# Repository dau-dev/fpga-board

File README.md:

# fpga-board
Based on the Xilinx AC701 and KC705 reference designs, this board was created to address the dearth of PCIe and DDR SODIMM capable board for less than $1000.

##Features
- Artix 7 FPGA (160k)
- 4GB DDR3 SODIMM
- 256MB Quad SPI Flash
- 8Kb IIC EEPROM
- SD Card Slot
- 2x 10/100/1000 Mbps Ethernet
- PCI Express 4 Lane
- Onboard JTAG
- Fixed Oscillator with differential 200MHz output
- User Programmable (IIC) Differential Oscillator (Range: 10MHz - 810 MHz, 156.250 MHz default)
- ATX Power 
- Half-Length PCI Card form factor

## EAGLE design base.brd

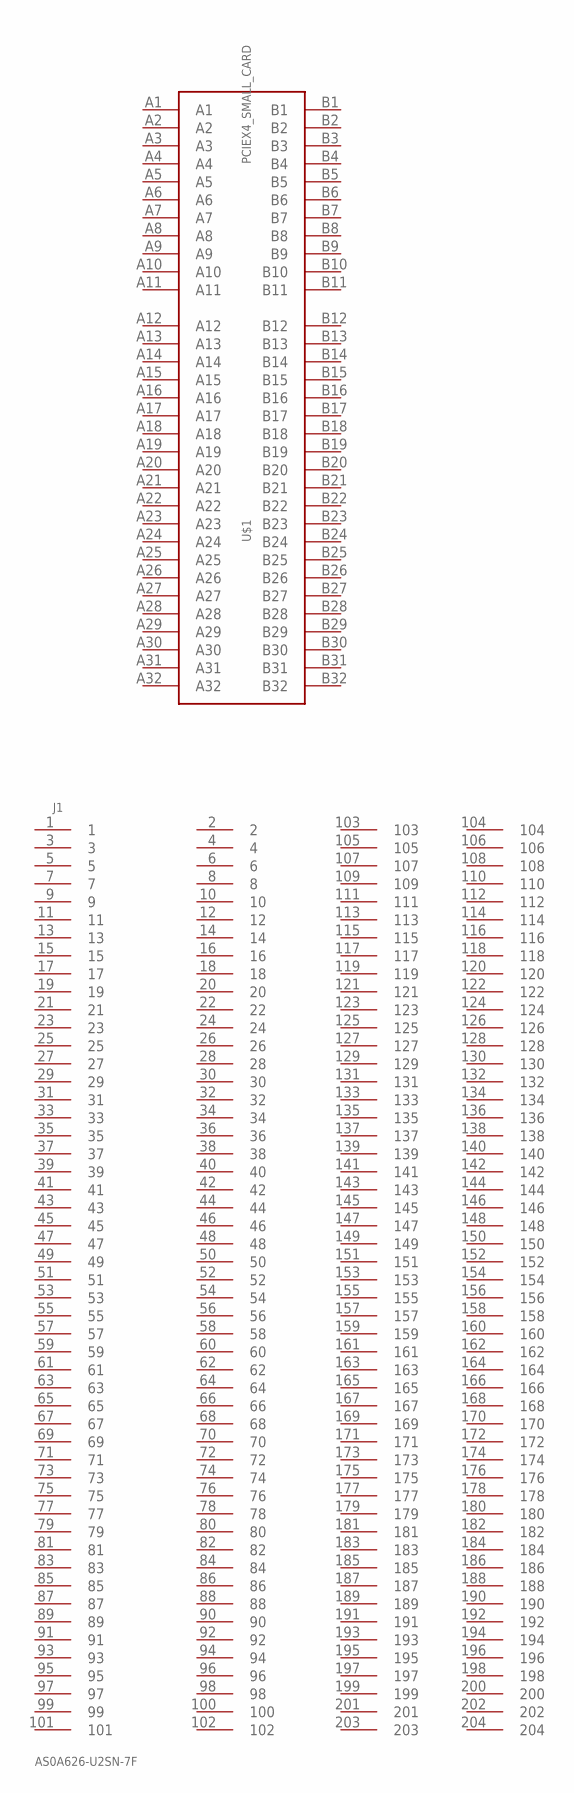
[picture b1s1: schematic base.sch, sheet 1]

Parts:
J1: AS0A626-U2SN-7F; FOXCONN_AS0A626-U2SN-7F
U$1: PCIEX4_SMALL_CARD

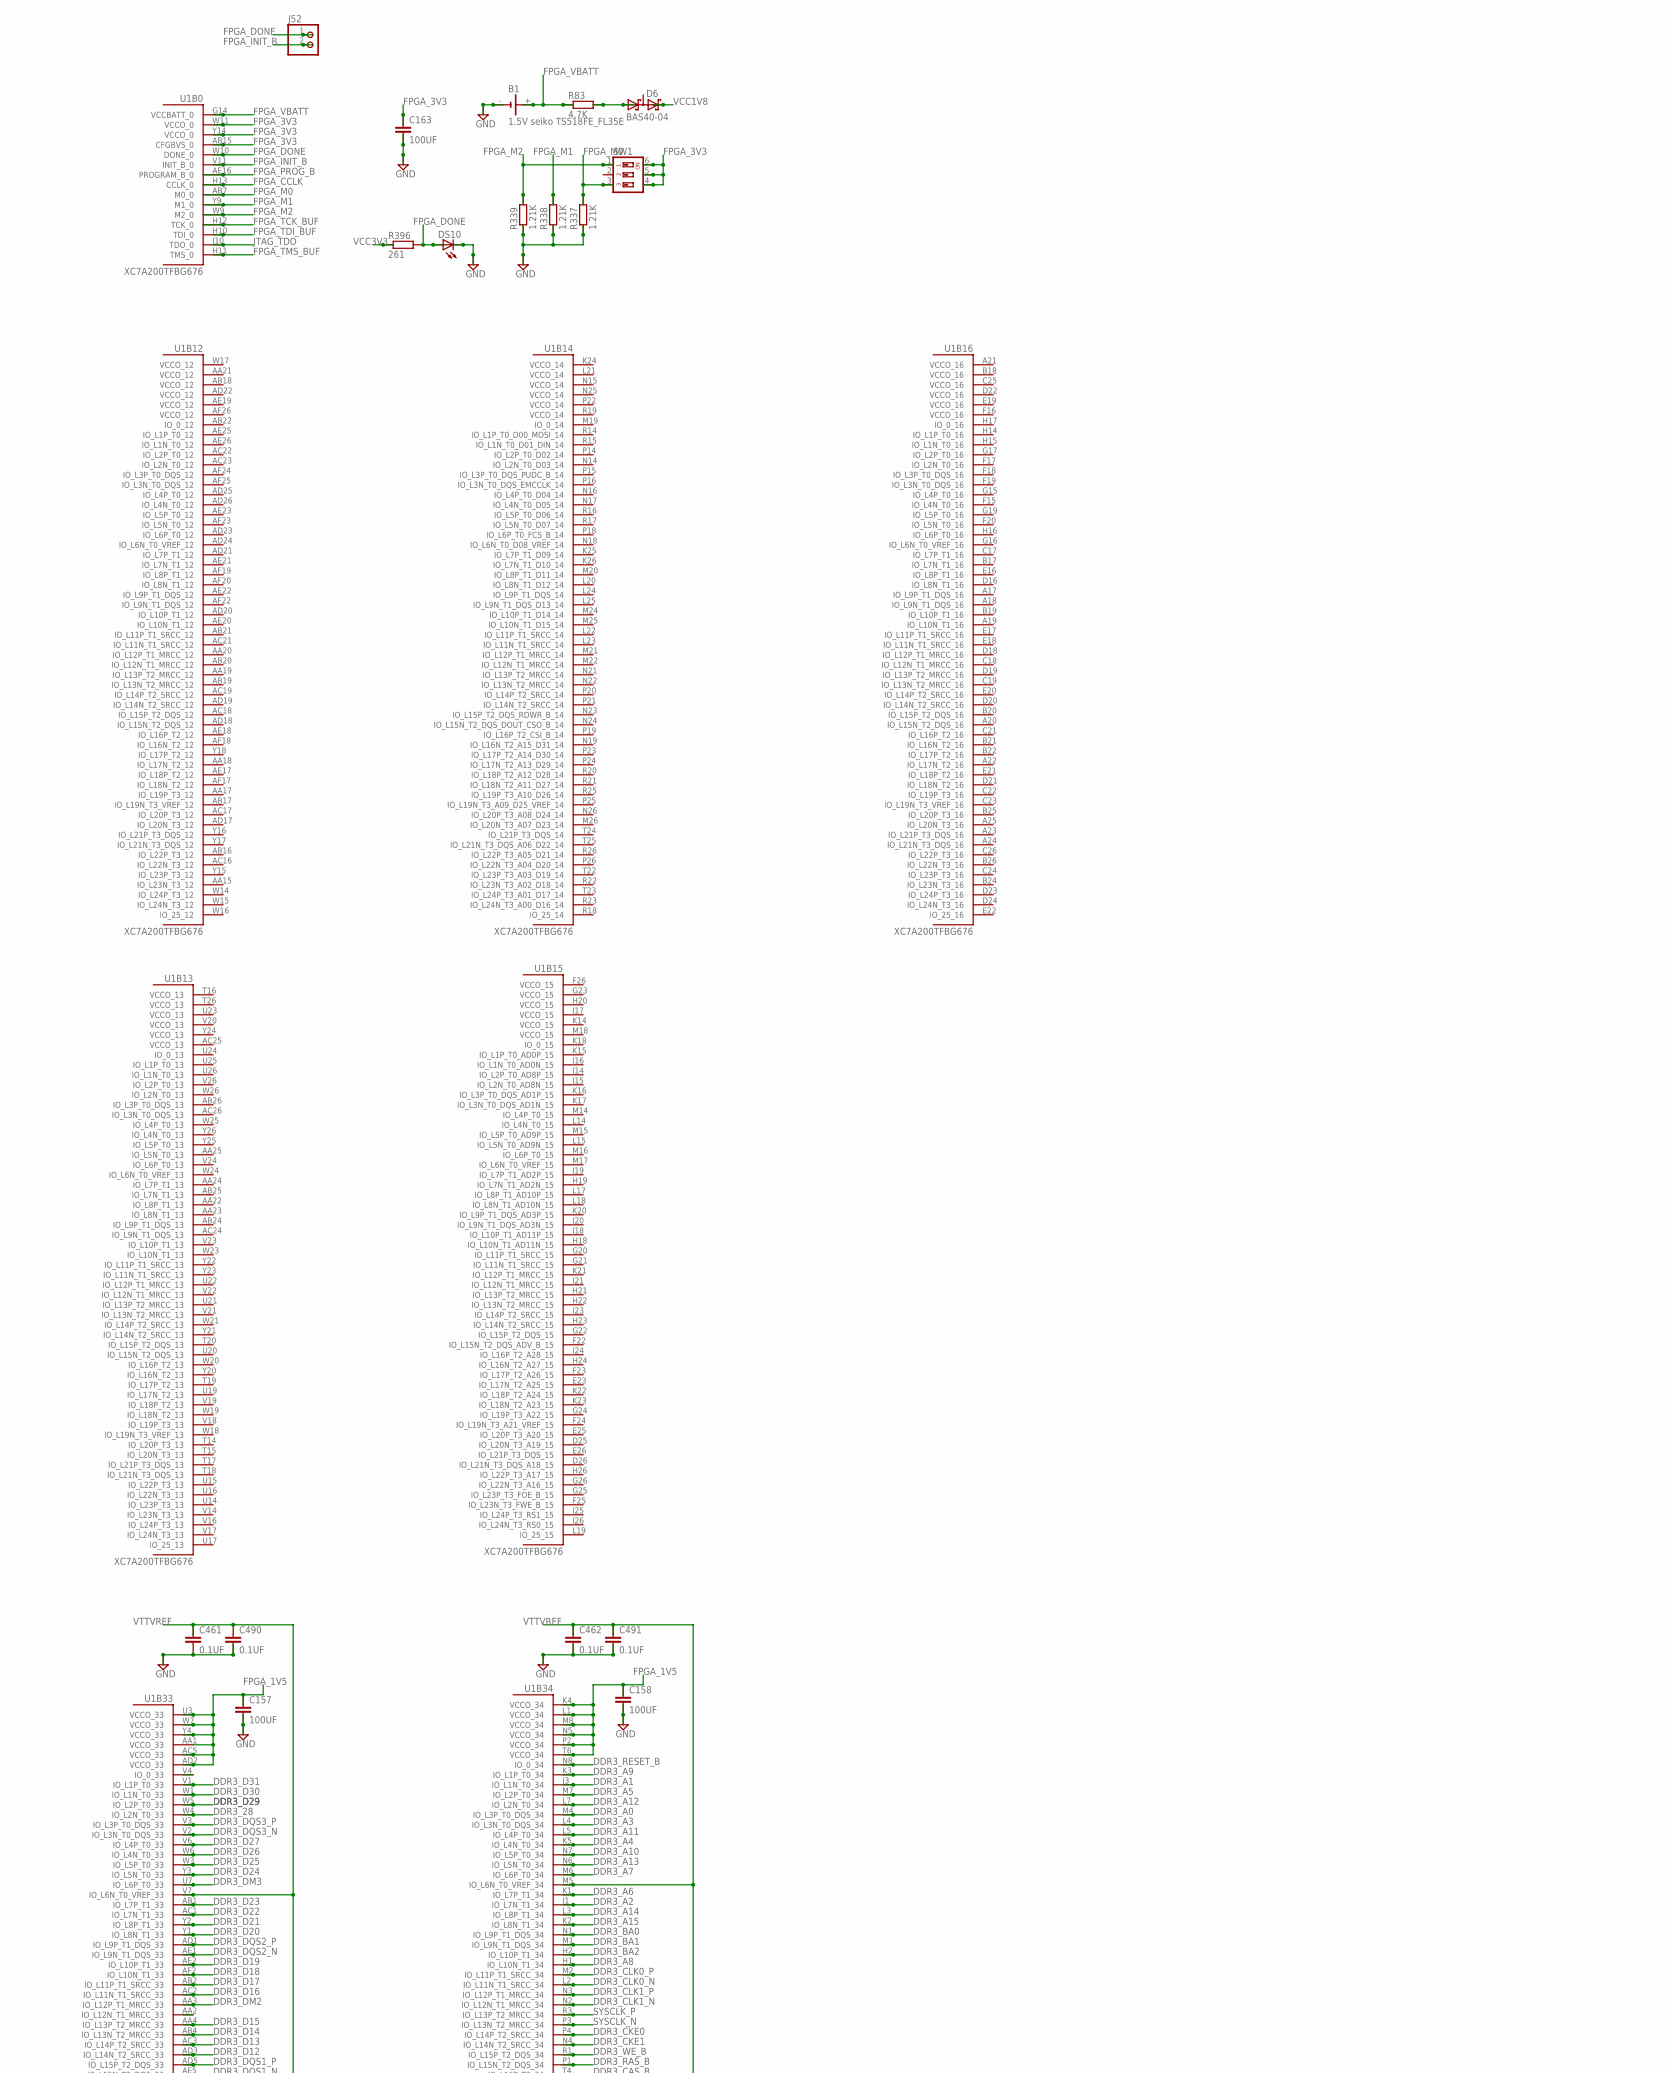
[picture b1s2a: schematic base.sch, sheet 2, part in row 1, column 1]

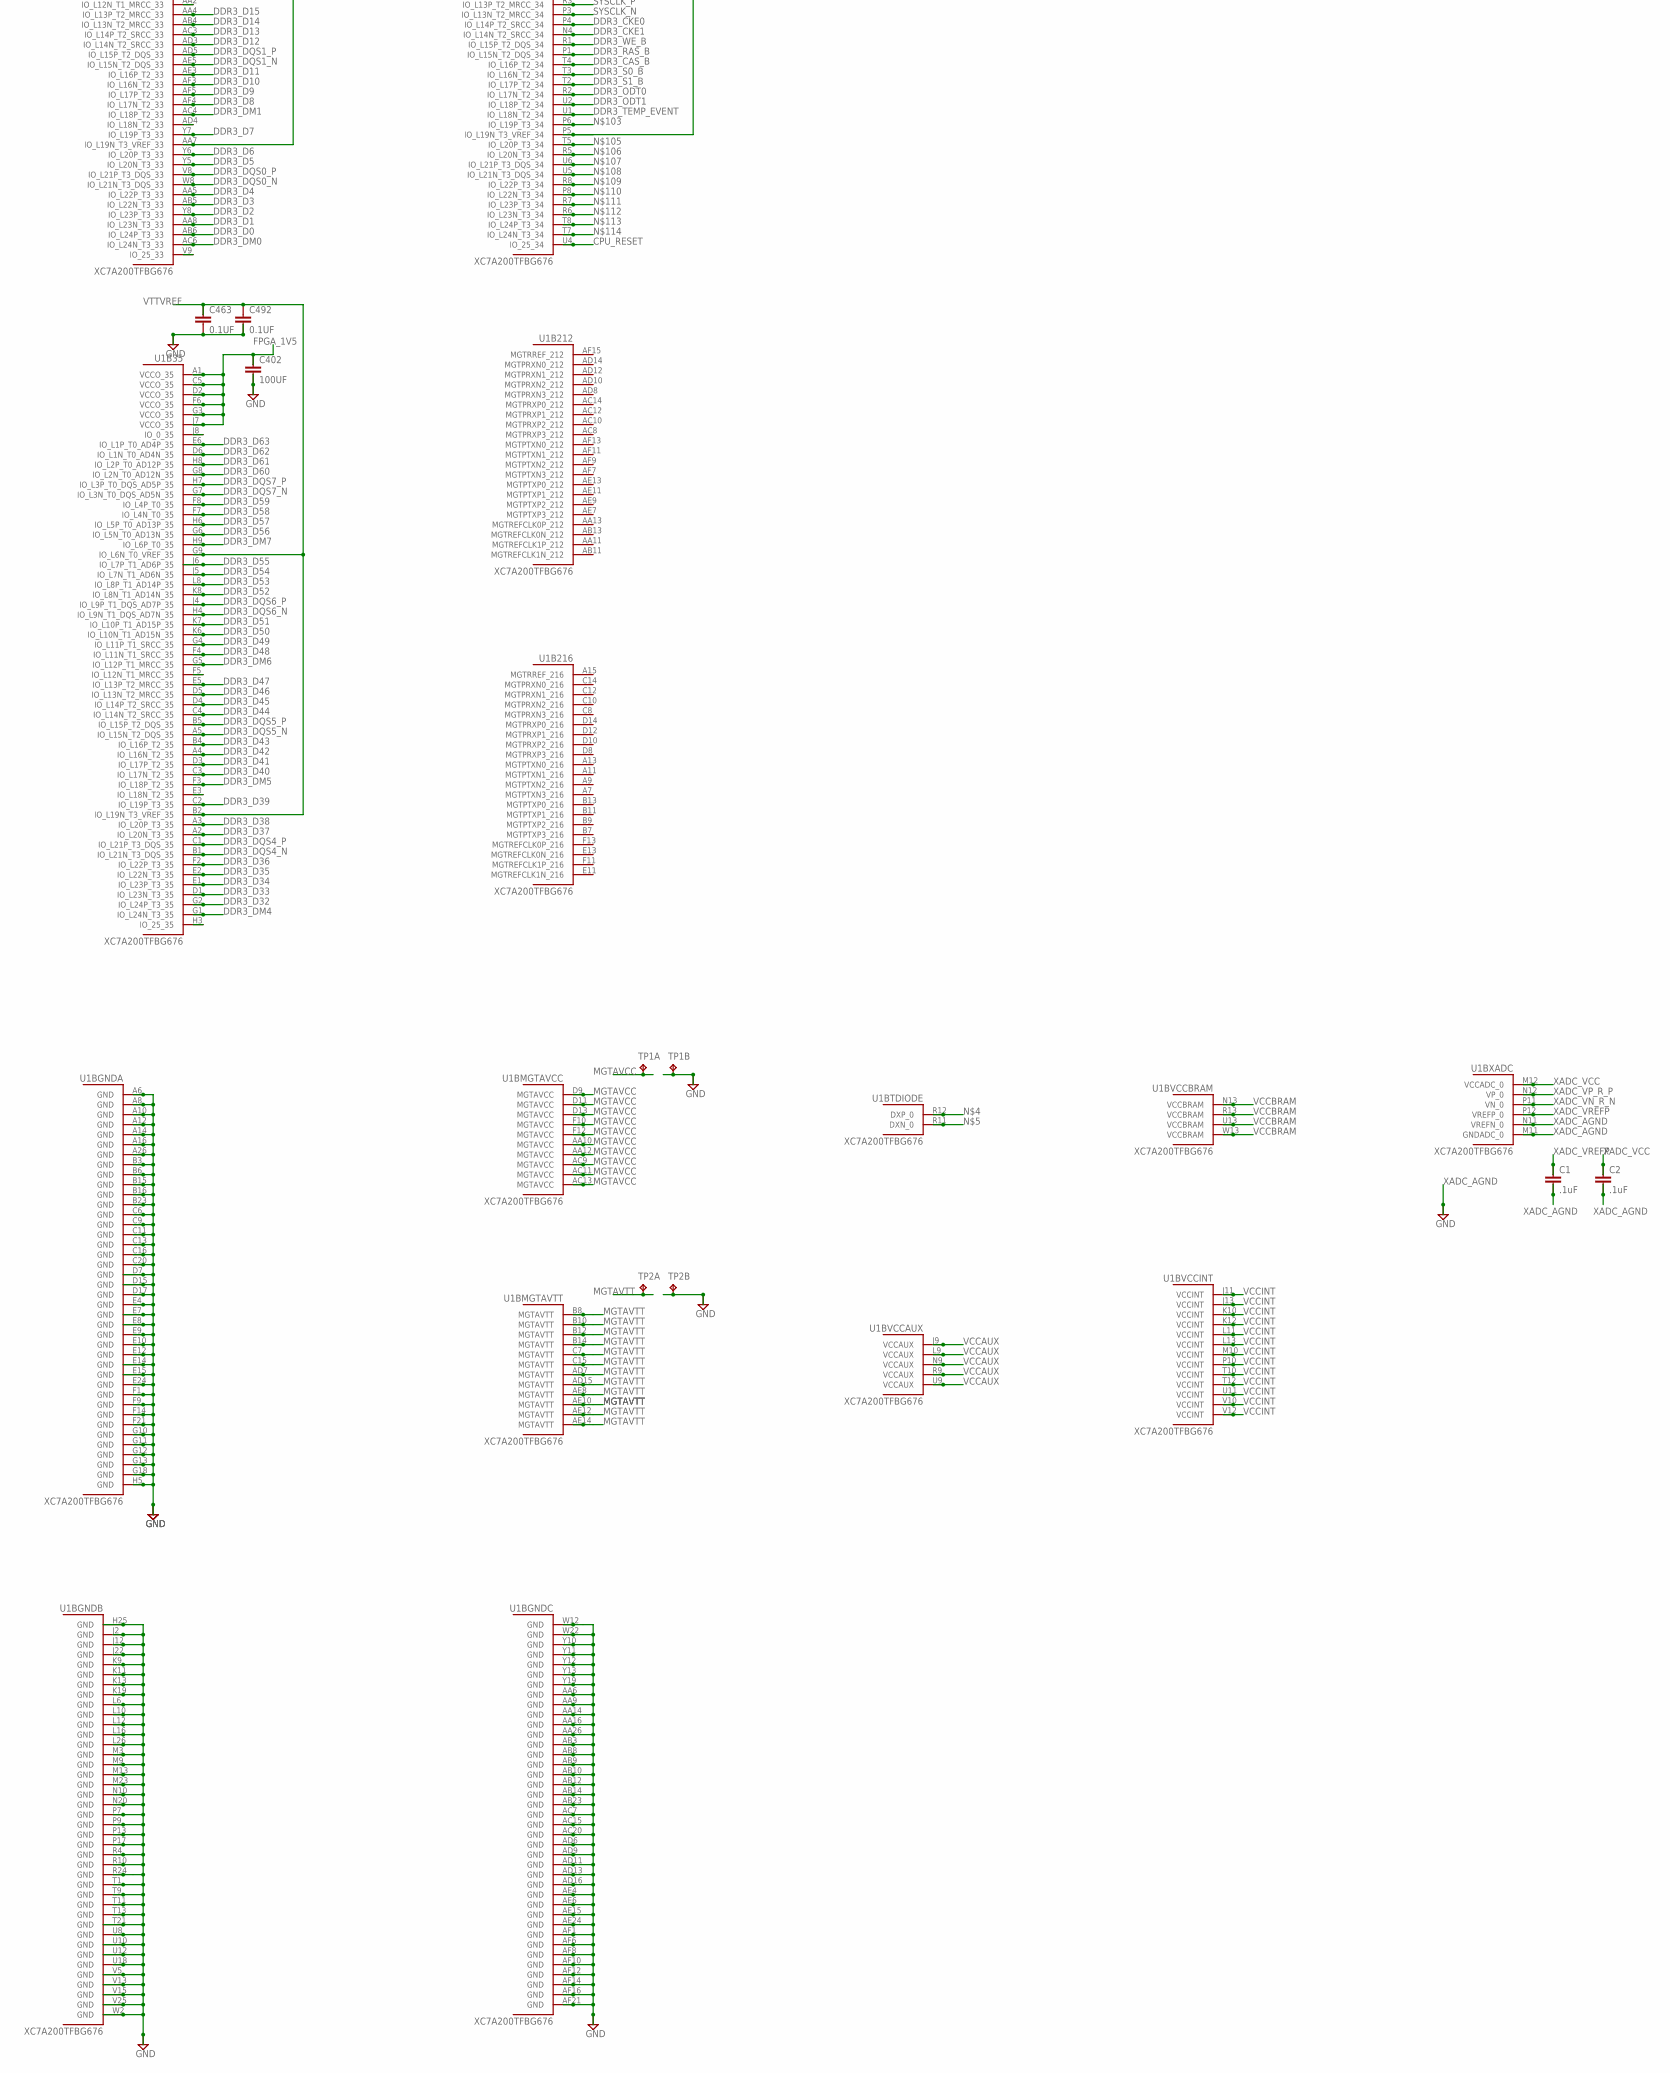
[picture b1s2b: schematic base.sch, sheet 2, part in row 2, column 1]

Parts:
B1: 1.5V seiko TS518FE_FL35E; CH291-1220LF
C1, C2: .1uF; C0402
C157, C158, C163, C402: 100UF; C1206
C461, C462, C463, C490, C491, C492: 0.1UF; C0402
D6: BAS40-04; SOT23
DS10: LEDCHIP-LED0603; CHIP-LED0603
J52: PINHD-1X2; 1X02
R83: 4.7K; R0402
R337, R338, R339: 1.21K; R0402
R396: 261; R0402
SW1: SWS003; SMS-003
TP1, TP2: TP2P2-38-17; P2-38-17
U1: XC7A200TFBG676; FF676

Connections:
CPU_RESET: U1.U4 (IO_25_34)
DDR3_28: U1.W4 (IO_L2N_T0_33)
DDR3_A0: U1.M4 (IO_L3P_T0_DQS_34)
DDR3_A1: U1.J3 (IO_L1N_T0_34)
DDR3_A2: U1.J1 (IO_L7N_T1_34)
DDR3_A3: U1.L4 (IO_L3N_T0_DQS_34)
DDR3_A4: U1.K5 (IO_L4N_T0_34)
DDR3_A5: U1.M7 (IO_L2P_T0_34)
DDR3_A6: U1.K1 (IO_L7P_T1_34)
DDR3_A7: U1.M6 (IO_L6P_T0_34)
DDR3_A8: U1.H1 (IO_L10N_T1_34)
DDR3_A9: U1.K3 (IO_L1P_T0_34)
DDR3_A10: U1.N7 (IO_L5P_T0_34)
DDR3_A11: U1.L5 (IO_L4P_T0_34)
DDR3_A12: U1.L7 (IO_L2N_T0_34)
DDR3_A13: U1.N6 (IO_L5N_T0_34)
DDR3_A14: U1.L3 (IO_L8P_T1_34)
DDR3_A15: U1.K2 (IO_L8N_T1_34)
DDR3_BA0: U1.N1 (IO_L9P_T1_DQS_34)
DDR3_BA1: U1.M1 (IO_L9N_T1_DQS_34)
DDR3_BA2: U1.H2 (IO_L10P_T1_34)
DDR3_CAS_B: U1.T4 (IO_L16P_T2_34)
DDR3_CKE0: U1.P4 (IO_L14P_T2_SRCC_34)
DDR3_CKE1: U1.N4 (IO_L14N_T2_SRCC_34)
DDR3_CLK0_N: U1.L2 (IO_L11N_T1_SRCC_34)
DDR3_CLK0_P: U1.M2 (IO_L11P_T1_SRCC_34)
DDR3_CLK1_N: U1.N2 (IO_L12N_T1_MRCC_34)
DDR3_CLK1_P: U1.N3 (IO_L12P_T1_MRCC_34)
DDR3_D0: U1.AB6 (IO_L24P_T3_33)
DDR3_D1: U1.AA8 (IO_L23N_T3_33)
DDR3_D2: U1.Y8 (IO_L23P_T3_33)
DDR3_D3: U1.AB5 (IO_L22N_T3_33)
DDR3_D4: U1.AA5 (IO_L22P_T3_33)
DDR3_D5: U1.Y5 (IO_L20N_T3_33)
DDR3_D6: U1.Y6 (IO_L20P_T3_33)
DDR3_D7: U1.Y7 (IO_L19P_T3_33)
DDR3_D8: U1.AF4 (IO_L17N_T2_33)
DDR3_D9: U1.AF5 (IO_L17P_T2_33)
DDR3_D10: U1.AF3 (IO_L16N_T2_33)
DDR3_D11: U1.AE3 (IO_L16P_T2_33)
DDR3_D12: U1.AD3 (IO_L14N_T2_SRCC_33)
DDR3_D13: U1.AC3 (IO_L14P_T2_SRCC_33)
DDR3_D14: U1.AB4 (IO_L13N_T2_MRCC_33)
DDR3_D15: U1.AA4 (IO_L13P_T2_MRCC_33)
DDR3_D16: U1.AC2 (IO_L11N_T1_SRCC_33)
DDR3_D17: U1.AB2 (IO_L11P_T1_SRCC_33)
DDR3_D18: U1.AF2 (IO_L10N_T1_33)
DDR3_D19: U1.AE2 (IO_L10P_T1_33)
DDR3_D20: U1.Y1 (IO_L8N_T1_33)
DDR3_D21: U1.Y2 (IO_L8P_T1_33)
DDR3_D22: U1.AC1 (IO_L7N_T1_33)
DDR3_D23: U1.AB1 (IO_L7P_T1_33)
DDR3_D24: U1.Y3 (IO_L5N_T0_33)
DDR3_D25: U1.W3 (IO_L5P_T0_33)
DDR3_D26: U1.W6 (IO_L4N_T0_33)
DDR3_D27: U1.V6 (IO_L4P_T0_33)
DDR3_D29: U1.W5 (IO_L2P_T0_33)
DDR3_D30: U1.W1 (IO_L1N_T0_33)
DDR3_D31: U1.V1 (IO_L1P_T0_33)
DDR3_D32: U1.G2 (IO_L24P_T3_35)
DDR3_D33: U1.D1 (IO_L23N_T3_35)
DDR3_D34: U1.E1 (IO_L23P_T3_35)
DDR3_D35: U1.E2 (IO_L22N_T3_35)
DDR3_D36: U1.F2 (IO_L22P_T3_35)
DDR3_D37: U1.A2 (IO_L20N_T3_35)
DDR3_D38: U1.A3 (IO_L20P_T3_35)
DDR3_D39: U1.C2 (IO_L19P_T3_35)
DDR3_D40: U1.C3 (IO_L17N_T2_35)
DDR3_D41: U1.D3 (IO_L17P_T2_35)
DDR3_D42: U1.A4 (IO_L16N_T2_35)
DDR3_D43: U1.B4 (IO_L16P_T2_35)
DDR3_D44: U1.C4 (IO_L14N_T2_SRCC_35)
DDR3_D45: U1.D4 (IO_L14P_T2_SRCC_35)
DDR3_D46: U1.D5 (IO_L13N_T2_MRCC_35)
DDR3_D47: U1.E5 (IO_L13P_T2_MRCC_35)
DDR3_D48: U1.F4 (IO_L11N_T1_SRCC_35)
DDR3_D49: U1.G4 (IO_L11P_T1_SRCC_35)
DDR3_D50: U1.K6 (IO_L10N_T1_AD15N_35)
DDR3_D51: U1.K7 (IO_L10P_T1_AD15P_35)
DDR3_D52: U1.K8 (IO_L8N_T1_AD14N_35)
DDR3_D53: U1.L8 (IO_L8P_T1_AD14P_35)
DDR3_D54: U1.J5 (IO_L7N_T1_AD6N_35)
DDR3_D55: U1.J6 (IO_L7P_T1_AD6P_35)
DDR3_D56: U1.G6 (IO_L5N_T0_AD13N_35)
DDR3_D57: U1.H6 (IO_L5P_T0_AD13P_35)
DDR3_D58: U1.F7 (IO_L4N_T0_35)
DDR3_D59: U1.F8 (IO_L4P_T0_35)
DDR3_D60: U1.G8 (IO_L2N_T0_AD12N_35)
DDR3_D61: U1.H8 (IO_L2P_T0_AD12P_35)
DDR3_D62: U1.D6 (IO_L1N_T0_AD4N_35)
DDR3_D63: U1.E6 (IO_L1P_T0_AD4P_35)
DDR3_DM0: U1.AC6 (IO_L24N_T3_33)
DDR3_DM1: U1.AC4 (IO_L18P_T2_33)
DDR3_DM2: U1.AA3 (IO_L12P_T1_MRCC_33)
DDR3_DM3: U1.U7 (IO_L6P_T0_33)
DDR3_DM4: U1.G1 (IO_L24N_T3_35)
DDR3_DM5: U1.F3 (IO_L18P_T2_35)
DDR3_DM6: U1.G5 (IO_L12P_T1_MRCC_35)
DDR3_DM7: U1.H9 (IO_L6P_T0_35)
DDR3_DQS0_N: U1.W8 (IO_L21N_T3_DQS_33)
DDR3_DQS0_P: U1.V8 (IO_L21P_T3_DQS_33)
DDR3_DQS1_N: U1.AE5 (IO_L15N_T2_DQS_33)
DDR3_DQS1_P: U1.AD5 (IO_L15P_T2_DQS_33)
DDR3_DQS2_N: U1.AE1 (IO_L9N_T1_DQS_33)
DDR3_DQS2_P: U1.AD1 (IO_L9P_T1_DQS_33)
DDR3_DQS3_N: U1.V2 (IO_L3N_T0_DQS_33)
DDR3_DQS3_P: U1.V3 (IO_L3P_T0_DQS_33)
DDR3_DQS4_N: U1.B1 (IO_L21N_T3_DQS_35)
DDR3_DQS4_P: U1.C1 (IO_L21P_T3_DQS_35)
DDR3_DQS5_N: U1.A5 (IO_L15N_T2_DQS_35)
DDR3_DQS5_P: U1.B5 (IO_L15P_T2_DQS_35)
DDR3_DQS6_N: U1.H4 (IO_L9N_T1_DQS_AD7N_35)
DDR3_DQS6_P: U1.J4 (IO_L9P_T1_DQS_AD7P_35)
DDR3_DQS7_N: U1.G7 (IO_L3N_T0_DQS_AD5N_35)
DDR3_DQS7_P: U1.H7 (IO_L3P_T0_DQS_AD5P_35)
DDR3_ODT0: U1.R2 (IO_L17N_T2_34)
DDR3_ODT1: U1.U2 (IO_L18P_T2_34)
DDR3_RAS_B: U1.P1 (IO_L15N_T2_DQS_34)
DDR3_RESET_B: U1.N8 (IO_0_34)
DDR3_S0_B: U1.T3 (IO_L16N_T2_34)
DDR3_S1_B: U1.T2 (IO_L17P_T2_34)
DDR3_TEMP_EVENT: U1.U1 (IO_L18N_T2_34)
DDR3_WE_B: U1.R1 (IO_L15P_T2_DQS_34)
FPGA_1V5: C157.1, C158.1, C402.1, U1.AA1 (VCCO_33), U1.AC5 (VCCO_33), U1.AD2 (VCCO_33), U1.F6 (VCCO_35), U1.K4 (VCCO_34), U1.L1 (VCCO_34), U1.M8 (VCCO_34), U1.N5 (VCCO_34), U1.P2 (VCCO_34), U1.T6 (VCCO_34), U1.U3 (VCCO_33), U1.W7 (VCCO_33), U1.Y4 (VCCO_33)
FPGA_3V3: C163.1, SW1.4, SW1.5, SW1.6, U1.AB15 (CFGBVS_0), U1.W11 (VCCO_0), U1.Y14 (VCCO_0)
FPGA_CCLK: U1.H13 (CCLK_0)
FPGA_DONE: DS10.A, J52.1, R396.2, U1.W10 (DONE_0)
FPGA_INIT_B: J52.2, U1.V11 (INIT_B_0)
FPGA_M0: R337.2, SW1.3, U1.AB7 (M0_0)
FPGA_M1: R338.2, U1.Y9 (M1_0)
FPGA_M2: R339.2, SW1.1, U1.W9 (M2_0)
FPGA_PROG_B: U1.AE16 (PROGRAM_B_0)
FPGA_TCK_BUF: U1.H12 (TCK_0)
FPGA_TDI_BUF: U1.H10 (TDI_0)
FPGA_TMS_BUF: U1.H11 (TMS_0)
FPGA_VBATT: B1.+, R83.1, U1.G14 (VCCBATT_0)
GND: B1.-, C157.2, C158.2, C163.2, C402.2, C461.2, C462.2, C463.2, C490.2, C491.2, C492.2, DS10.C, R337.1, R338.1, R339.1, TP1.TP-2, TP2.TP-2, U1.A6 (GND), U1.A8 (GND), U1.A10 (GND), U1.A12 (GND), U1.A14 (GND), U1.A16 (GND), U1.A26 (GND), U1.AA6 (GND), U1.AA9 (GND), U1.AA14 (GND), U1.AA16 (GND), U1.AA26 (GND), U1.AB3 (GND), U1.AB8 (GND), U1.AB9 (GND), U1.AB10 (GND), U1.AB12 (GND), U1.AB14 (GND), U1.AB23 (GND), U1.AC7 (GND), U1.AC15 (GND), U1.AC20 (GND), U1.AD6 (GND), U1.AD9 (GND), U1.AD11 (GND), U1.AD13 (GND), U1.AD16 (GND), U1.AE4 (GND), U1.AE6 (GND), U1.AE15 (GND), U1.AE24 (GND), U1.AF1 (GND), U1.AF6 (GND), U1.AF8 (GND), U1.AF10 (GND), U1.AF12 (GND), U1.AF14 (GND), U1.AF16 (GND), U1.AF21 (GND), U1.B3 (GND), U1.B6 (GND), U1.B15 (GND), U1.B16 (GND), U1.B23 (GND), U1.C6 (GND), U1.C9 (GND), U1.C11 (GND), U1.C13 (GND), U1.C16 (GND), U1.C20 (GND), U1.D7 (GND), U1.D15 (GND), U1.D17 (GND), U1.E4 (GND), U1.E7 (GND), U1.E8 (GND), U1.E9 (GND), U1.E10 (GND), U1.E12 (GND), U1.E14 (GND), U1.E15 (GND), U1.E24 (GND), U1.F1 (GND), U1.F9 (GND), U1.F14 (GND), U1.F21 (GND), U1.G10 (GND), U1.G11 (GND), U1.G12 (GND), U1.G13 (GND), U1.G18 (GND), U1.H5 (GND), U1.H25 (GND), U1.J2 (GND), U1.J12 (GND), U1.J22 (GND), U1.K9 (GND), U1.K11 (GND), U1.K13 (GND), U1.K19 (GND), U1.L6 (GND), U1.L10 (GND), U1.L12 (GND), U1.L16 (GND), U1.L26 (GND), U1.M3 (GND), U1.M9 (GND), U1.M13 (GND), U1.M23 (GND), U1.N10 (GND), U1.N20 (GND), U1.P7 (GND), U1.P9 (GND), U1.P13 (GND), U1.P17 (GND), U1.R4 (GND), U1.R10 (GND), U1.R24 (GND), U1.T1 (GND), U1.T9 (GND), U1.T11 (GND), U1.T13 (GND), U1.T21 (GND), U1.U8 (GND), U1.U10 (GND), U1.U12 (GND), U1.U18 (GND), U1.V5 (GND), U1.V13 (GND), U1.V15 (GND), U1.V25 (GND), U1.W2 (GND), U1.W12 (GND), U1.W22 (GND), U1.Y10 (GND), U1.Y11 (GND), U1.Y12 (GND), U1.Y13 (GND), U1.Y19 (GND)
JTAG_TDO: U1.J10 (TDO_0)
MGTAVCC: TP1.TP-1, U1.AA10 (MGTAVCC), U1.AA12 (MGTAVCC), U1.AC9 (MGTAVCC), U1.AC11 (MGTAVCC), U1.AC13 (MGTAVCC), U1.D9 (MGTAVCC), U1.D11 (MGTAVCC), U1.D13 (MGTAVCC), U1.F10 (MGTAVCC), U1.F12 (MGTAVCC)
MGTAVTT: TP2.TP-1, U1.AD7 (MGTAVTT), U1.AD15 (MGTAVTT), U1.AE8 (MGTAVTT), U1.AE10 (MGTAVTT), U1.AE12 (MGTAVTT), U1.AE14 (MGTAVTT), U1.B8 (MGTAVTT), U1.B10 (MGTAVTT), U1.B12 (MGTAVTT), U1.B14 (MGTAVTT), U1.C7 (MGTAVTT), U1.C15 (MGTAVTT)
unnamed: D6.1 (A1), R83.2
SYSCLK_N: U1.P3 (IO_L13N_T2_MRCC_34)
SYSCLK_P: U1.R3 (IO_L13P_T2_MRCC_34)
VCC1V8: D6.2 (C2)
VCC3V3: R396.1
VCCAUX: U1.J9 (VCCAUX), U1.L9 (VCCAUX), U1.N9 (VCCAUX), U1.R9 (VCCAUX), U1.U9 (VCCAUX)
VCCBRAM: U1.N13 (VCCBRAM), U1.R13 (VCCBRAM), U1.U13 (VCCBRAM), U1.W13 (VCCBRAM)
VCCINT: U1.J11 (VCCINT), U1.J13 (VCCINT), U1.K10 (VCCINT), U1.K12 (VCCINT), U1.L11 (VCCINT), U1.L13 (VCCINT), U1.M10 (VCCINT), U1.P10 (VCCINT), U1.T10 (VCCINT), U1.T12 (VCCINT), U1.U11 (VCCINT), U1.V10 (VCCINT), U1.V12 (VCCINT)
VTTVREF: C461.1, C462.1, C463.1, C490.1, C491.1, C492.1, U1.AA7 (IO_L19N_T3_VREF_33), U1.B2 (IO_L19N_T3_VREF_35), U1.G9 (IO_L6N_T0_VREF_35), U1.M5 (IO_L6N_T0_VREF_34), U1.P5 (IO_L19N_T3_VREF_34), U1.V7 (IO_L6N_T0_VREF_33)
XADC_AGND: C1.2, C2.2, U1.M11 (GNDADC_0), U1.N11 (VREFN_0)
XADC_VCC: C2.1, U1.M12 (VCCADC_0)
XADC_VN_R_N: U1.P11 (VN_0)
XADC_VP_R_P: U1.N12 (VP_0)
XADC_VREFP: C1.1, U1.P12 (VREFP_0)

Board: 2 copper layers, 27 parts (0 on the bottom side), 19 nets, no tracks yet.

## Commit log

2016-09-03 adding base board and schematic for minimal kintex 160 fpga
2016-09-04 adding DRAM.
2016-09-04 updates to DRAM.
2016-09-05 dram wired.
2016-09-05 reverting dram, bigger chip.
2016-09-06 Adding docs, adding pins, adding bom.
2016-09-08 updating pins for sd, eeprom, flash, rj45.
2016-09-09 updated with caps, resistors, inductors, and switches up to page 34
2016-09-10 updated BOM and pin list
2016-09-14 README updates
2016-12-01 updating for new lib.
2016-12-07 updates, wired 33 + 34
2016-12-07 adding 35
2016-12-07 downgrading fpga in readme.
2018-08-01 Create LICENSE
